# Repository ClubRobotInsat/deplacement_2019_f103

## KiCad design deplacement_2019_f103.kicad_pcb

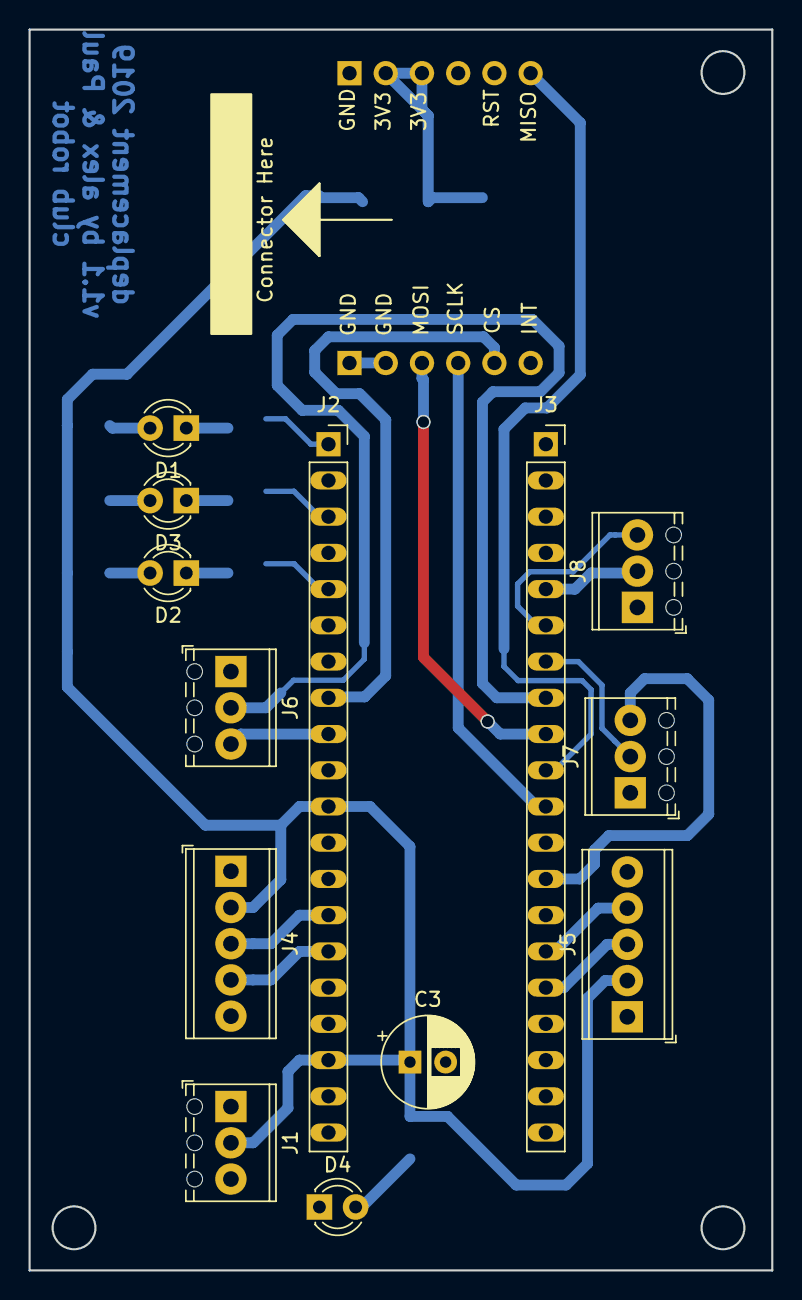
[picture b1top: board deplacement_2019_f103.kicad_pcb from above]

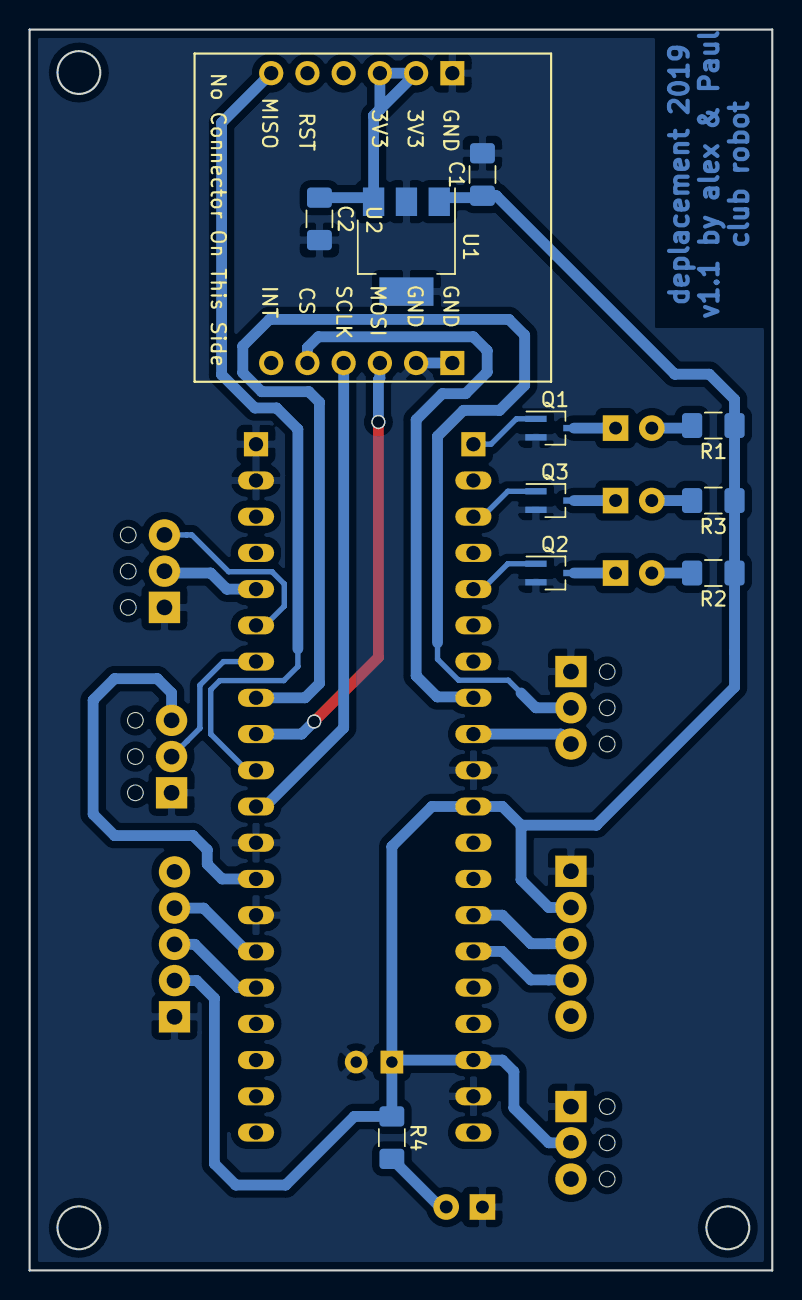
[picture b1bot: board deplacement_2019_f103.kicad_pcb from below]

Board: 2 copper layers, 52.1 x 87.0 mm, 24 parts (10 on the bottom side), 27 nets.

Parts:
C1, C2: 1u; C_1206_3216Metric_Pad1.42x1.75mm_HandSolder
C3: 100uF; CP_Radial_D6.3mm_P2.50mm
D1: LED_hardfault_jaune; LED_D3.0mm
D2: LED_communication_vert; LED_D3.0mm
D3: LED_ucontrolleur_vert; LED_D3.0mm
D4: LED_alimentation_rouge; LED_D3.0mm
J1: Alim logique; TerminalBlock_Phoenix_MPT-0,5-3-2.54_1x03_P2.54mm_Horizontal
J2: Connecteur Gauche; PinSocket_1x20_P2.54mm_Vertical_Long_Pads
J3: Connecteur Droit; PinSocket_1x20_P2.54mm_Vertical_Long_Pads
J4, J5: Conn_01x05; TerminalBlock_Phoenix_MPT-0,5-5-2.54_1x05_P2.54mm_Horizontal
J6, J7: PWM output; TerminalBlock_Phoenix_MPT-0,5-3-2.54_1x03_P2.54mm_Horizontal
J8: Liaison serie; TerminalBlock_Phoenix_MPT-0,5-3-2.54_1x03_P2.54mm_Horizontal
Q1, Q2, Q3: PMF370XN; SOT-323_SC-70_Handsoldering
R1, R2, R3, R4: 150; R_1206_3216Metric_Pad1.42x1.75mm_HandSolder
U1: TC1262-33; SOT-223-3_TabPin2
U2: w5500

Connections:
+3V3: C2.1, U1.3, U2.10, U2.11
+5V: C1.1, C3.1, J1.2, J2.11, J2.18, J4.2, J5.2, R1.1, R2.1, R3.1, R4.1, U1.1
/CS: J2.8, U2.2
/MISO: J3.10, U2.7
/MOSI: J3.9, U2.4
/RX: J3.5, J8.2
/SCLK: J3.11, U2.3
/TX: J3.6, J8.3
/led_communication: J2.5, Q2.1
/led_feedback: J2.3, Q3.1
/led_hardfault: J2.1, Q1.1
/motor_left_PWM: J3.8, J6.2
/motor_left_direction: J2.9, J6.3
/motor_right_PWM: J3.7, J7.2
/motor_right_direction: J3.13, J7.3
/qei_left_A: J2.14, J4.3
/qei_left_B: J2.15, J4.4
/qei_right_A: J3.16, J5.3
/qei_right_B: J3.15, J5.4
GND: C1.2, C2.2, C3.2, D4.1, J1.1, J2.10, J2.19, J3.1, J3.2, J3.12, J3.14, J4.1, J5.1, J6.1, J7.1, J8.1, Q1.2, Q2.2, Q3.2, U1.2, U2.5, U2.6, U2.12
unnamed: D1.1, Q1.3
unnamed: D1.2, R1.2
unnamed: D2.1, Q2.3
unnamed: D2.2, R2.2
unnamed: D3.1, Q3.3
unnamed: D3.2, R3.2
unnamed: D4.2, R4.2

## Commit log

2018-11-25 First revision.
2018-11-25 Fix invalid PCB.
2019-01-16 added ethernet connector
2019-01-17 fixed routing mistake
2019-01-20 Integrate w5500 change
2019-01-21 Updated the entire PCB to the previous w5500 change
2019-01-21 Added testpoints
2019-01-21 removed an floating wire
2019-01-21 actually save the files
2019-02-06 fix the schematic. The board is still not working
2019-02-06 place footprints
2019-02-06 complete the pcb
2019-02-06 add the board's dimensions
2019-02-06 update the final pcb typon and fix a ground issue
2019-03-07 Fix wrong pinout for PWM pins
2019-05-16 Add version number on schematic and PCB Add vias for top cables
2019-05-16 Add missing version number on pcb
2019-05-16 Add missing drill holes
2019-05-16 Update footprints and board
2019-05-17 Fix connectors
